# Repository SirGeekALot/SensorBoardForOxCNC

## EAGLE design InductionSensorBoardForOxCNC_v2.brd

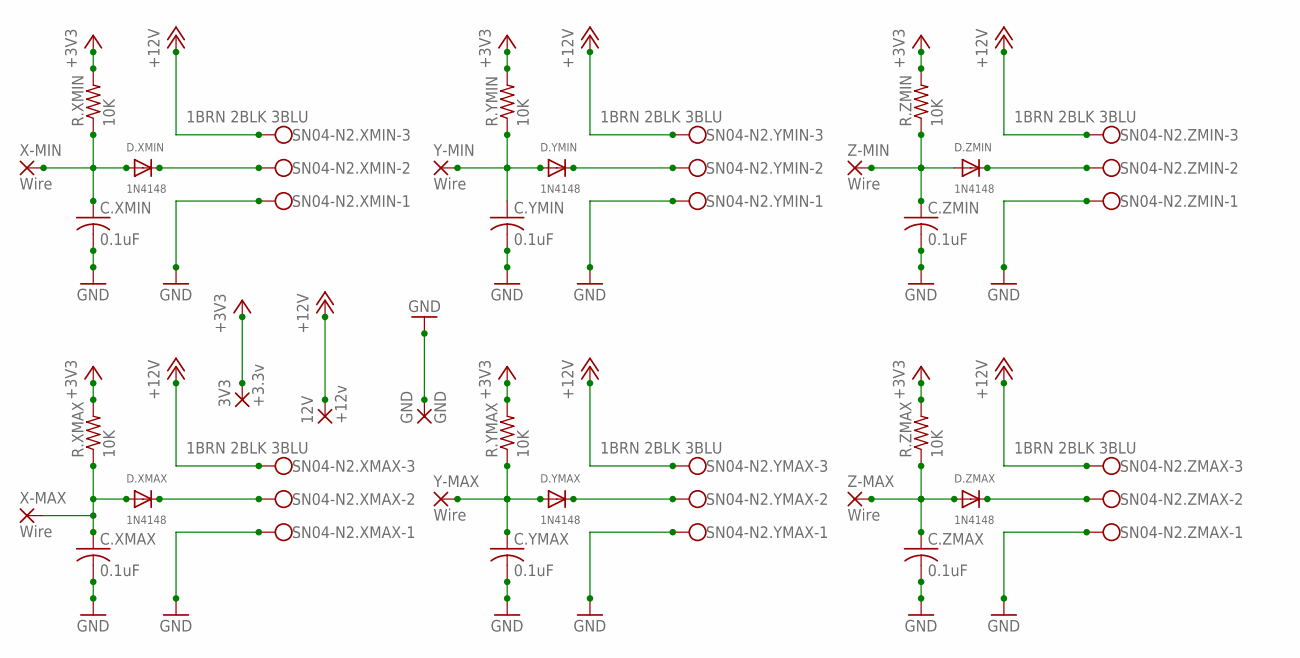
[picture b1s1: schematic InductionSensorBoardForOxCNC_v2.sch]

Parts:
3V3: +3.3v; 3,81/1,4
12V: +12v; 3,81/1,4
C.XMAX, C.XMIN, C.YMAX, C.YMIN, C.ZMAX, C.ZMIN: 0.1uF; C050-024X044
D.XMAX, D.XMIN, D.YMAX, D.YMIN, D.ZMAX, D.ZMIN: 1N4148; DO-1N4148
GND: GND; 3,81/1,4
R.XMAX, R.XMIN, R.YMAX, R.YMIN, R.ZMAX, R.ZMIN: 10K; 0207/10
SN04-N2.XMAX, SN04-N2.XMIN, SN04-N2.YMAX, SN04-N2.YMIN, SN04-N2.ZMAX, SN04-N2.ZMIN: 1BRN 2BLK 3BLU; W237-103
X-MAX: Wire; 3,81/1,1
X-MIN: Wire; 3,81/1,1
Y-MAX: Wire; 3,81/1,1
Y-MIN: Wire; 3,81/1,1
Z-MAX: Wire; 3,81/1,1
Z-MIN: Wire; 3,81/1,1

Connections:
+3V3: 3V3.1, R.XMAX.2, R.XMIN.2, R.YMAX.2, R.YMIN.2, R.ZMAX.2, R.ZMIN.2
+12V: 12V.1, SN04-N2.XMAX.3, SN04-N2.XMIN.3, SN04-N2.YMAX.3, SN04-N2.YMIN.3, SN04-N2.ZMAX.3, SN04-N2.ZMIN.3
GND: C.XMAX.2, C.XMIN.2, C.YMAX.2, C.YMIN.2, C.ZMAX.2, C.ZMIN.2, GND.1, SN04-N2.XMAX.1, SN04-N2.XMIN.1, SN04-N2.YMAX.1, SN04-N2.YMIN.1, SN04-N2.ZMAX.1, SN04-N2.ZMIN.1
unnamed: C.XMIN.1, D.XMIN.A, R.XMIN.1, X-MIN.1
unnamed: D.XMIN.C, SN04-N2.XMIN.2
unnamed: C.YMIN.1, D.YMIN.A, R.YMIN.1, Y-MIN.1
unnamed: D.YMIN.C, SN04-N2.YMIN.2
unnamed: C.YMAX.1, D.YMAX.A, R.YMAX.1, Y-MAX.1
unnamed: D.YMAX.C, SN04-N2.YMAX.2
unnamed: C.XMAX.1, D.XMAX.A, R.XMAX.1, X-MAX.1
unnamed: D.XMAX.C, SN04-N2.XMAX.2
unnamed: C.ZMIN.1, D.ZMIN.A, R.ZMIN.1, Z-MIN.1
unnamed: D.ZMIN.C, SN04-N2.ZMIN.2
unnamed: C.ZMAX.1, D.ZMAX.A, R.ZMAX.1, Z-MAX.1
unnamed: D.ZMAX.C, SN04-N2.ZMAX.2

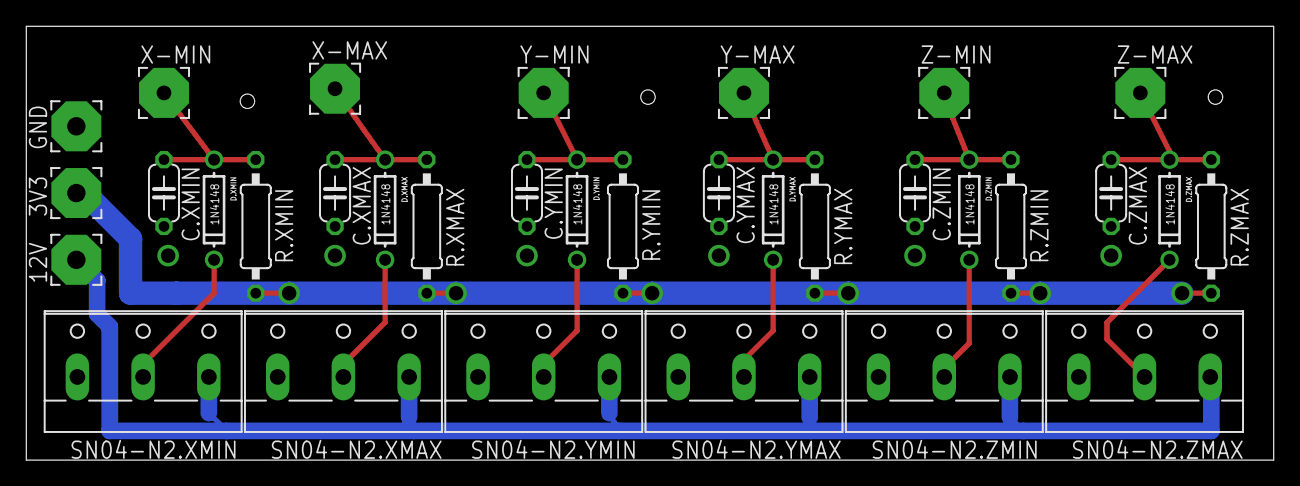
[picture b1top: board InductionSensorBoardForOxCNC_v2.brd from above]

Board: 2 copper layers, 94.9 x 33.0 mm, 33 parts (0 on the bottom side), 15 nets.

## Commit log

2015-12-27 My first attempt at using Eagle
    I've created a board to help make adding min/max induction sensors for
    X, Y, and Z axes on my OpenBuilds Ox CNC router. This design uses
    SN04-02 induction sensors for use with a TinyG v8 controller board, and
    is intended to prevent false triggers by filtering out EMF from the
    spindle. DISCLAIMER: this is my first EVER attempt at using Eagle, and I
    have NOT built or tried this circuit yet. I'm posting this so it can be
2015-12-31 Added board layout and schematic jpg files
    Added board layout and schematic jpg files to help expedite review.
